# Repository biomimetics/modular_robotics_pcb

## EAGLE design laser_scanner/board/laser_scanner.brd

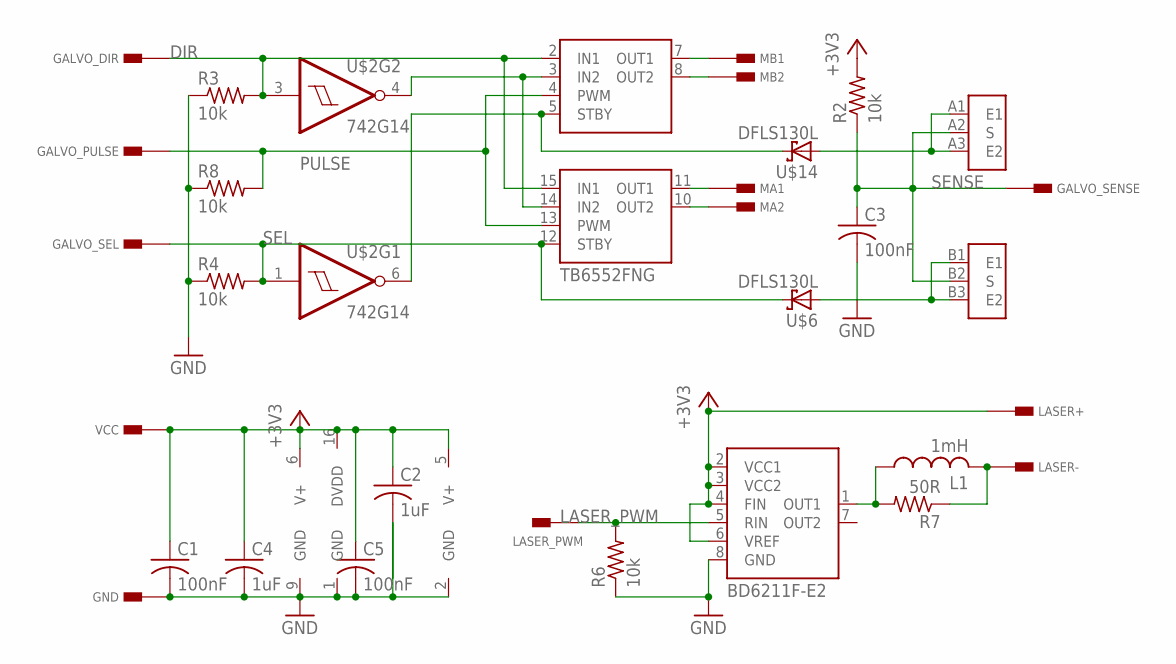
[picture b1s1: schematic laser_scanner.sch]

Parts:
C1, C3, C5: 100nF; C0603
C2, C4: 1uF; C0603
GALVO_DIR: PAD-0.6_1.8; PAD_0.6_1.8
GALVO_PULSE: PAD-0.6_1.8; PAD_0.6_1.8
GALVO_SEL: PAD-0.6_1.8; PAD_0.6_1.8
GALVO_SENSE: PAD-0.6_1.8; PAD_0.6_1.8
GND: PAD-0.6_1.8; PAD_0.6_1.8
L1: 1mH; L7070
LASER+: PAD-0.6_1.8; PAD_0.6_1.8
LASER-: PAD-0.6_1.8; PAD_0.6_1.8
LASER_PWM: PAD-0.6_1.8; PAD_0.6_1.8
MA1, MA2: PAD-0.6_1.8; PAD_0.6_1.8
MB1, MB2: PAD-0.6_1.8; PAD_0.6_1.8
R2, R3, R4, R6, R8: 10k; R0603
R7: 50R; R0603
U$1: TB6552; TSSOP16
U$2: 742G14; SOT23-6
U$3: BD6211; SOP-08
U$6, U$14: DFLS130L; POWERDI323
U$7: LASER_SLIDER; LASER_SCANNER
VCC: PAD-0.6_1.8; PAD_0.6_1.8

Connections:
+3V3: C1.1, C2.1, C4.1, C5.1, LASER+.1, R2.2, U$1.6 (V+), U$1.16 (DVDD), U$2.5 (V+), U$3.2 (VCC1), U$3.3 (VCC2), U$3.4 (FIN), U$3.6 (VREF), VCC.1
DIR: GALVO_DIR.1, R3.2, U$1.2 (IN1), U$1.15 (IN1), U$2.3 (I)
GND: C1.2, C2.2, C3.2, C4.2, C5.2, GND.1, R3.1, R4.1, R6.1, R8.1, U$1.1 (GND), U$1.9 (GND), U$2.2 (GND), U$3.8 (GND)
LASER_PWM: LASER_PWM.1, R6.2, U$3.5 (RIN)
unnamed: MB1.1, U$1.7 (OUT1)
unnamed: MB2.1, U$1.8 (OUT2)
unnamed: MA1.1, U$1.11 (OUT1)
unnamed: MA2.1, U$1.10 (OUT2)
unnamed: U$1.3 (IN2), U$1.14 (IN2), U$2.4 (O)
unnamed: U$7.A1 (E1), U$7.A3 (E2), U$14.A
unnamed: L1.1, R7.2, U$3.1 (OUT1)
unnamed: U$6.A, U$7.B1 (E1), U$7.B3 (E2)
unnamed: L1.2, LASER-.1, R7.1
unnamed: U$1.5 (STBY), U$2.6 (O), U$14.C
PULSE: GALVO_PULSE.1, R8.2, U$1.4 (PWM), U$1.13 (PWM)
SEL: GALVO_SEL.1, R4.2, U$1.12 (STBY), U$2.1 (I), U$6.C
SENSE: C3.1, GALVO_SENSE.1, R2.1, U$7.A2 (S), U$7.B2 (S)

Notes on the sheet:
BD6211F-E2
TB6552FNG

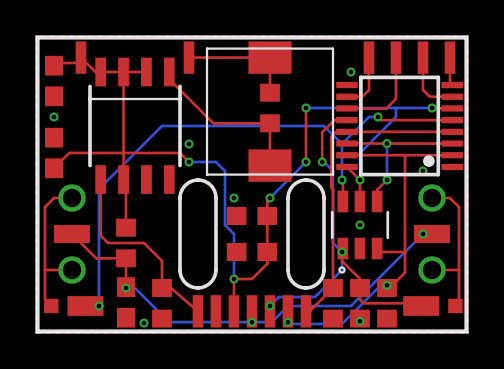
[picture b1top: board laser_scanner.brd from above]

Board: 2 copper layers, 24.0 x 16.5 mm, 31 parts (0 on the bottom side), 17 nets.

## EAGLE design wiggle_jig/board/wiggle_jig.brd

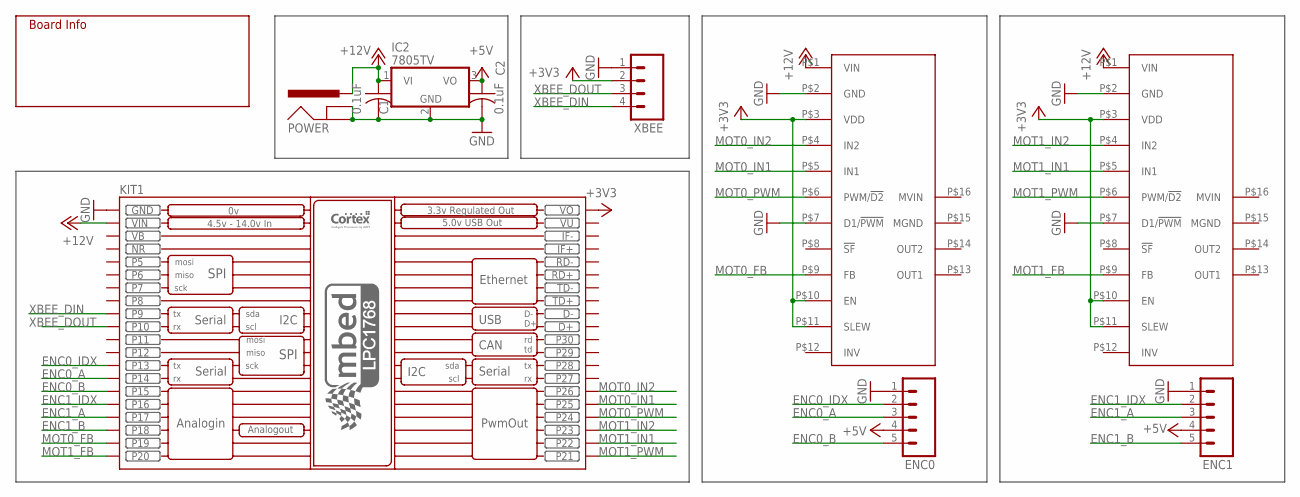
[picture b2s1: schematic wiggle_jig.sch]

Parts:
C1, C2: 0.1uF; C025-025X050
ENC0, ENC1: M05LOCK; 1X05_LOCK
IC2: 7805TV; TO220V
KIT1: MBED_NXP_LPC1768; MBED-KIT
MOT0, MOT1: MC33926_CARRIER
POWER: POWER_JACKPTH_LOCK; POWER_JACK_PTH_LOCK
U$4: INFO
XBEE: M04LOCK; 1X04_LOCK

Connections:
+3V3: KIT1.VOUT (VO), MOT0.P$3 (VDD), MOT0.P$10 (EN), MOT0.P$11 (SLEW), MOT1.P$3 (VDD), MOT1.P$10 (EN), MOT1.P$11 (SLEW), XBEE.2
+5V: C2.1, ENC0.4, ENC1.4, IC2.3 (VO)
+12V: C1.1, IC2.1 (VI), KIT1.VIN, MOT0.P$1 (VIN), MOT1.P$1 (VIN), POWER.PWR
ENC0_A: ENC0.3, KIT1.P$14 (P14)
ENC0_B: ENC0.5, KIT1.P$15 (P15)
ENC0_IDX: ENC0.2, KIT1.P$13 (P13)
ENC1_A: ENC1.3, KIT1.P$17 (P17)
ENC1_B: ENC1.5, KIT1.P$18 (P18)
ENC1_IDX: ENC1.2, KIT1.P$16 (P16)
GND: C1.2, C2.2, ENC0.1, ENC1.1, IC2.2 (GND), KIT1.GND, MOT0.P$2 (GND), MOT0.P$7 (D1/!PWM), MOT1.P$2 (GND), MOT1.P$7 (D1/!PWM), POWER.GND, POWER.GNDBREAK, XBEE.1
MOT0_FB: KIT1.P$19 (P19), MOT0.P$9 (FB)
MOT0_IN1: KIT1.P$25 (P25), MOT0.P$5 (IN1)
MOT0_IN2: KIT1.P$26 (P26), MOT0.P$4 (IN2)
MOT0_PWM: KIT1.P$24 (P24), MOT0.P$6 (PWM/!D2)
MOT1_FB: KIT1.P$20 (P20), MOT1.P$9 (FB)
MOT1_IN1: KIT1.P$22 (P22), MOT1.P$5 (IN1)
MOT1_IN2: KIT1.P$23 (P23), MOT1.P$4 (IN2)
MOT1_PWM: KIT1.P$21 (P21), MOT1.P$6 (PWM/!D2)
NR: KIT1.NR
VB: KIT1.VB
VU: KIT1.VU
XBEE_DIN: KIT1.P$9 (P9), XBEE.4
XBEE_DOUT: KIT1.P$10 (P10), XBEE.3

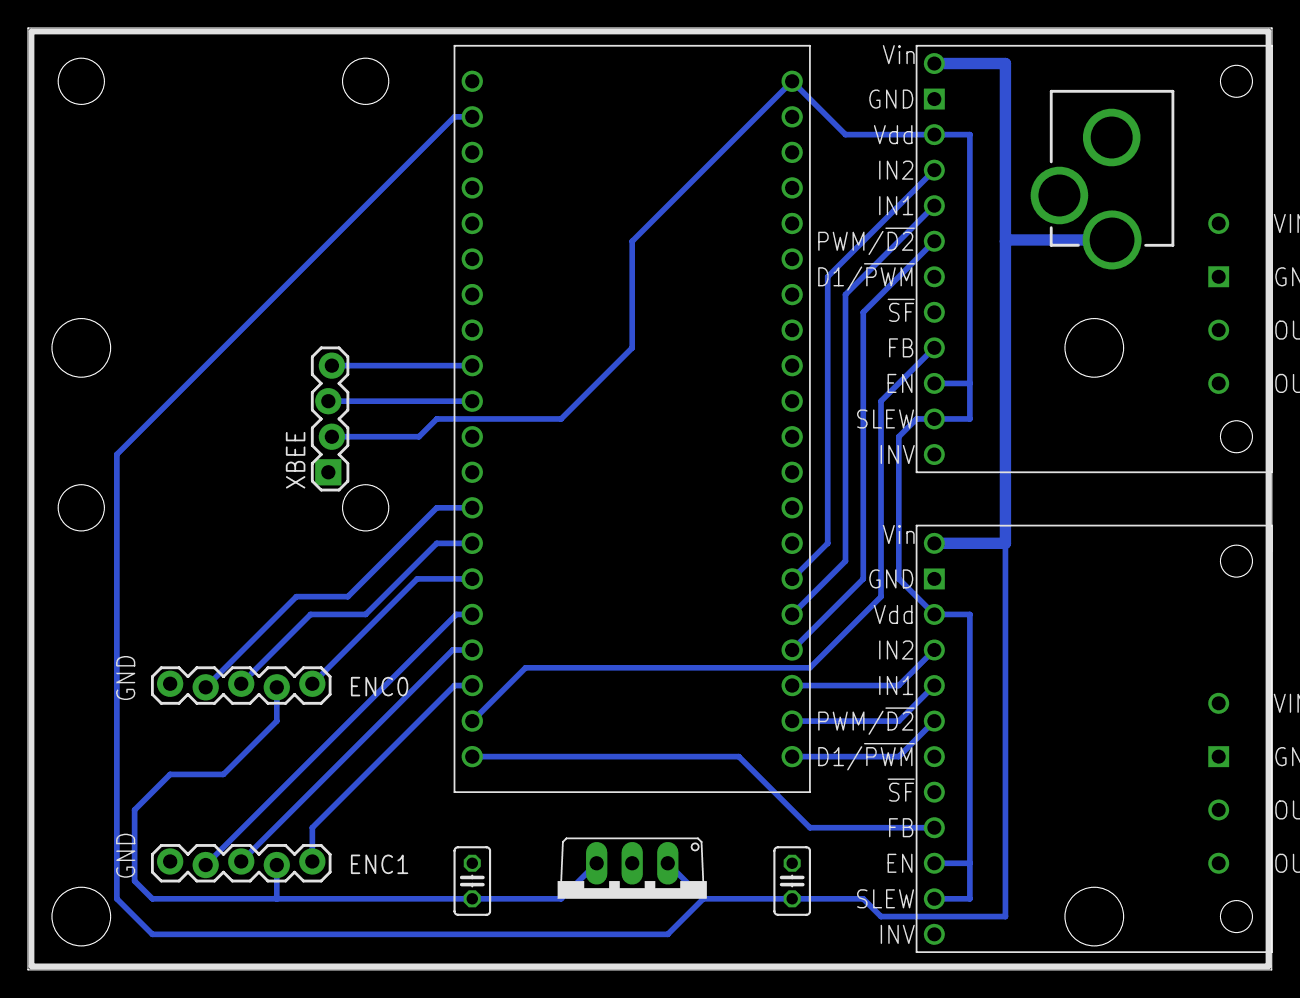
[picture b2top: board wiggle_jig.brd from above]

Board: 2 copper layers, 88.9 x 67.3 mm, 15 parts (0 on the bottom side), 20 nets.

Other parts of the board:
U$1, U$2, U$3, U$9: STAND-OFF

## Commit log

2017-04-21 First pass at Othermilled laser scanner board. About to update for Bay Area Circuits order.
2017-04-23 Reworked laser scanner for BAC order
2017-05-04 Adding panelized laser scanner board.
2017-05-04 Added labels to wires. Fixed signal running through ground via.
2017-08-04 Made laser scanner more readable.

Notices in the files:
parts and their libraries:
SparkFun-Connectors: Licensing: CC v3.0 Share-Alike You are welcome to use this library for commercial purposes.
